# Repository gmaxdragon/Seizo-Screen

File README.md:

# Seizo Screen

Seizo Screen is a screen with a bunch of extra features that I find extremely useful for my robotic arm. There are lots of minor issues that are extremely annoying to work around, and this is my solution.

I want a screen so I can run direct motor controls without having to connect through my phone and worry about connections. I also wanted more features and wanted to make the whole thing look cooler.

## How I want to use it

During an arm session, I want to look at the screen and press a few buttons instead of doing everything on my phone. I want a "Run Arm" button that starts the arm setup. Keeping those controls on the arm would make it more independent. When this becomes a real product, I don't want using a phone to be required.

I want manual buttons for things like:

- Moving the base.
- Moving the wrist left and right.
- Opening and closing the gripper.
- Running the arm setup.

Eventually, I also want to let AI figure out the movements. The plan is to give it a prompt, have it convert that into individual movements, and then have the arm carry them out. This is something I'm planning to work on, and I think it would make everything much easier to use.

## The design challenge

One massive problem was organizing the components. I had to keep reorganizing them because none of the layouts seemed to be to my liking.

I originally had a much smaller PCB with fewer features. It felt like something that would take barely five minutes or so to put together, and it didn't seem cool enough to me. As a result, I changed it a lot by adding more features and making the PCB bigger.

I wanted things like a built-in meter and a breadboard area on the board. Making the PCB bigger gave me more room to do things like that. I'm planning to keep working on it and make it great.

## What I want to do next

Before the screen works with the arm, I need to do some basic sanity checks and make sure it works before connecting it to the arm. I might also try showing the Pi's output on it or adding some kind of built-in remote terminal, which would be extremely cool in my opinion.

I spent this summer designing and building the arm and worked on it almost every day. It has been extremely hard and difficult for me, and I want to make sure it works properly.

This has been my dream project for about a year, and I've struggled to find funding for all of it. I would really appreciate it if this project were accepted.

To be honest, soldering all the parts together by hand is extremely risky for me and it will take hours. I'd rather spend that time coding and making changes by hand and testing so I would like this to be presoldered please.

## Files

The Half-Life parts list had an 80-item (row) limit, so I used a grouped list for the submission. [Real_BOM.csv](Real_BOM.csv) contains the full ungrouped details, including each of the 150 fitted panel components, the screen, wiring and mounting items. It also identifies the matching HAT as a separate required dependency. [00-bom-halflife.csv](00-bom-halflife.csv) is the 27-row file for importing into Half-Life. Blank factory prices in the detailed BOM mean the quote is still pending, not that the parts are free.

- [Full detailed BOM](Real_BOM.csv)
- [KiCad project](szscreen.kicad_pro), [schematic](szscreen.kicad_sch) and [PCB](szscreen.kicad_pcb)
- [Schematic PDF](schematic.pdf)
- [Half-Life grouped BOM import](00-bom-halflife.csv) â€” 27 essential panel items within the 80-item limit; [import instructions](HALFLIFE-BOM-IMPORT.txt)
- [Earlier grouped project inventory](PROJECT-PARTS.csv) and [PCBWay preliminary price screenshot](quotes/pcbway/preliminary-calculator.png)
- [Parts list](BOM-panel.csv) and [connector pin map](CONNECTOR-PIN-MAP.csv)
- [Factory assembly BOM](assembly/BOM-PCBWay-panel.csv), [matching-HAT BOM](assembly/BOM-PCBWay-matching-HAT.csv), [DigiKey import CSV](assembly/DigiKey-panel-import.csv) and [assembly quote instructions](assembly/ORDER-INSTRUCTIONS.txt)
- [Factory quote upload ZIP](szscreen-PCBWay-turnkey-quote.zip)
- [Panel fabrication ZIP](szscreen-panel-Gerbers.zip)
- [Matching Pi HAT revision](matching-HAT/) and [assembly connections](ASSEMBLY-CONNECTIONS.txt)
- [Reference firmware](reference/firmware/) and [verification report](VERIFICATION.json)

## Contributions

The original schematic, PCB placement and full earlier routing were made by Vivaan, with his friend helping with ideas, parts, organization, routing and troubleshooting. ChatGPT/Codex helped with later schematic and PCB revisions, component and footprint selection, routing, checks and technical documentation. It generated the reference firmware from Vivaan's detailed behavior requirements. That code is reference only; Vivaan plans to write the actual implementation. The original earlier routing is preserved in [history/user-routed-rev19](history/user-routed-rev19/).

README narrative: my messages, with grammar and formatting fixed by AI.

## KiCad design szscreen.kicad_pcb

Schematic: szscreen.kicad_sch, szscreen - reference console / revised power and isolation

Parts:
C1, C2, C3, C4, C5, C6, C7, C8, C9, C10, C14, C16, C18, C19, C20, C21, C24, C25, C26, C28, C29, C31, C33, C34, C35, C36: 100n; C_Rect_L4.0mm_W2.5mm_P2.50mm
C15, C17, C30: 10u / 50V; CP_Radial_D5.0mm_P2.00mm
C22, C23: 1n; C_Rect_L4.0mm_W2.5mm_P2.50mm
C27: 4.7u / 50V; CP_Radial_D5.0mm_P2.00mm
C32: 100u / 16V; CP_Radial_D5.0mm_P2.00mm
D1: 3V3 POWER; LED_D3.0mm
D2: PROTO FAULT; LED_D3.0mm
D3, D4: BAT85; D_DO-35_SOD27_P7.62mm_Horizontal
D5: PROTO POWER; LED_D3.0mm
F1: MF-RHT050-0 / 500mA HOLD; Fuse_Bourns_MF-RHT050
H1, H2, H3, H4: M3 PANEL; MountingHole_3.2mm_M3
H5, H6, H7, H8: M3 LCD; MountingHole_3.2mm_M3
H9, H10, H11, H12: M2.5 PI STACK; MountingHole_2.7mm_M2.5
J1: TO HAT J7 / I2C AND IRQ; PinHeader_1x06_P2.54mm_Vertical
J2: WAVESHARE 16446 / 2.8in TOUCH; PinHeader_1x11_P2.54mm_Vertical
J3: AUX 1 / DRY NC ONLY; PinHeader_1x02_P2.54mm_Vertical
J4: AUX 2 / DRY NC ONLY; PinHeader_1x02_P2.54mm_Vertical
J5: TO HAT J6 / SPI; PinHeader_1x06_P2.54mm_Vertical
J6: TO HAT J5 / CONTROL; PinHeader_1x06_P2.54mm_Vertical
J7: 5V IN / FROM HAT J12; PinHeader_1x03_P2.54mm_Vertical
J8: EXISTING 5V FAN / PASS; PinHeader_1x03_P2.54mm_Vertical
J9: PROBE + / COMMON GND; PinHeader_1x02_P2.54mm_Vertical
J10: PROTO 5V / GND; PinHeader_1x02_P2.54mm_Vertical
J11: LCD ACTUAL VIO / GND TAP; PinHeader_1x02_P2.54mm_Vertical
J12: HAT J4.3 GPIO6 / J4.4 GPIO7; PinHeader_1x02_P2.54mm_Vertical
J13: HAT J10 POWER / 1 GND 2 3V3; PinHeader_1x02_P2.54mm_Vertical
K1: AQY212EH / INPUT DISCONNECT; DIP-4_W7.62mm
R1, R2, R3, R4, R5, R6, R7, R8, R17, R18, R31, R40, R41, R46, R47, R48, R58, R60, R68, R70, R71, R74, R75: 10k; R_Axial_DIN0207_L6.3mm_D2.5mm_P7.62mm_Horizontal
R9, R10, R11, R12, R13, R14, R15, R16, R19, R20, R49, R50, R51, R55, R61, R72: 1k; R_Axial_DIN0207_L6.3mm_D2.5mm_P7.62mm_Horizontal
R27, R28, R62: 2.2k; R_Axial_DIN0207_L6.3mm_D2.5mm_P7.62mm_Horizontal
R32, R33, R34, R63: 33; R_Axial_DIN0207_L6.3mm_D2.5mm_P7.62mm_Horizontal
R35, R36, R37, R38, R39, R56, R57, R64, R65, R66: 100; R_Axial_DIN0207_L6.3mm_D2.5mm_P7.62mm_Horizontal
R42, R69, R76, R77, R78, R79, R80, R81: 100k; R_Axial_DIN0207_L6.3mm_D2.5mm_P7.62mm_Horizontal
R43: 22k; R_Axial_DIN0207_L6.3mm_D2.5mm_P7.62mm_Horizontal
R44, R45, R73: 4.7k; R_Axial_DIN0207_L6.3mm_D2.5mm_P7.62mm_Horizontal
R52, R53: 49.9k / 0.1%; R_Axial_DIN0207_L6.3mm_D2.5mm_P10.16mm_Horizontal
R54: 10.0k / 0.1%; R_Axial_DIN0207_L6.3mm_D2.5mm_P10.16mm_Horizontal
R59: 330 / 1%; R_Axial_DIN0207_L6.3mm_D2.5mm_P7.62mm_Horizontal
R67: 210k / 1%; R_Axial_DIN0207_L6.3mm_D2.5mm_P10.16mm_Horizontal
SW1: F1; SW_TH_Tactile_Omron_B3F-100x
SW2: F2; SW_TH_Tactile_Omron_B3F-100x
SW3: F3; SW_TH_Tactile_Omron_B3F-100x
SW4: F4; SW_TH_Tactile_Omron_B3F-100x
SW5: F5; SW_TH_Tactile_Omron_B3F-100x
SW6: F6; SW_TH_Tactile_Omron_B3F-100x
SW7: F7; SW_TH_Tactile_Omron_B3F-100x
SW8: HOLD REQUEST; SW_TH_Tactile_Omron_B3F-100x
SW9: I/O RESET ONLY; SW_TH_Tactile_Omron_B3F-100x
SW10: F8; SW_TH_Tactile_Omron_B3F-100x
SW11: F9; SW_TH_Tactile_Omron_B3F-100x
SW12: F10; SW_TH_Tactile_Omron_B3F-100x
SW13: METER ENABLE; SW_CK_JS202011CQN_DPDT_Straight
SW14: PROTO 5V OFF / ON (100mA); SW_CK_JS202011CQN_DPDT_Straight
TP1: PANEL_3V3; TestPoint_THTPad_D1.5mm_Drill0.7mm
TP2: GND; TestPoint_THTPad_D1.5mm_Drill0.7mm
TP3: SCL; TestPoint_THTPad_D1.5mm_Drill0.7mm
TP4: SDA; TestPoint_THTPad_D1.5mm_Drill0.7mm
TP5: IO_RESET; TestPoint_THTPad_D1.5mm_Drill0.7mm
TP6: LCD_5V; TestPoint_THTPad_D1.5mm_Drill0.7mm
U1: MCP23017-E/SP / 0x20; DIP-28_W7.62mm
U2: MCP3202-BI/P; DIP-8_W7.62mm
U3: MCP6002-I/P; DIP-8_W7.62mm
U4: MCP1525-I/TO; TO-92_Inline_Wide
U5: TPS2553DBVR-1 / LATCH OFF; SOT-23-6
U6: Adafruit 4683 3V3 BUCK; PinHeader_1x04_P2.54mm_Vertical
U8, U9, U10: SN74LV125AN; DIP-14_W7.62mm
U11: SN74AHC14N; DIP-14_W7.62mm

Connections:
/ADC_CH0: C22.1, R56.2, U2.2 (CH0)
/ADC_CH1: C23.1, R57.2, U2.3 (CH1)
/ADC_CS: R58.2, R66.2, U2.1 (~CS/SHDN)
/ADC_MISO: R63.1, U2.6 (DOUT)
/ADC_MOSI: R64.2, U2.5 (DIN)
/ADC_SCLK: R65.2, U2.7 (CLK)
/BB_EN: R69.1, SW14.2 (B), U5.3 (EN)
/BB_FAULT: D2.1 (K), J12.2, R70.2, U5.4 (~FAULT)
/BB_ILIM: R67.1, U5.5 (ILIM)
/BB_ON: R68.2, SW14.1 (A)
/BTN1: R9.2, U1.21 (GPA0)
/BTN2: R10.2, U1.22 (GPA1)
/BTN3: R11.2, U1.23 (GPA2)
/BTN4: R12.2, U1.24 (GPA3)
/BTN5: R13.2, U1.25 (GPA4)
/BTN6: R14.2, U1.26 (GPA5)
/BTN7: R15.2, U1.27 (GPA6)
/BTN8: R49.2, U1.4 (GPB3)
/BTN9: R50.2, U1.5 (GPB4)
/BTN10: R51.2, U1.6 (GPB5)
/GND: C1.2, C2.2, C3.2, C4.2, C5.2, C6.2, C7.2, C8.2, C9.2, C10.2, C14.2, C15.2, C16.2, C17.2, C18.2, C19.2, C20.2, C21.2, C22.2, C23.2, C24.2, C25.2, C26.2, C27.2, C28.2, C29.2, C30.2, C31.2, C32.2, C33.2, C34.2, C35.2, C36.2, D1.1 (K), D3.2 (A), D5.1 (K), J1.6, J2.2, J3.2, J4.2, J5.6, J6.6, J7.2, J8.2, J9.2, J10.2, J11.2, J13.1, K1.2, R42.1, R54.2, R67.2, R69.2, R71.2, R73.2, R76.2, R77.2, R78.2, R79.2, R80.2, R81.2, SW1.2, SW2.2, SW3.2, SW4.2, SW5.2, SW6.2, SW7.2, SW8.2, SW9.2, SW10.2, SW11.2, SW12.2, SW13.4 (A), SW14.3 (C), TP2.1, U1.10 (V_{SS}), U1.15 (A0), U1.16 (A1), U1.17 (A2), U2.4 (VSS), U3.4 (V-), U4.1 (Vss), U5.2 (GND), U6.1, U8.7 (GND), U9.7 (GND), U9.12, U10.4, U10.5, U10.7 (GND), U10.9, U10.12, U11.7 (GND), U11.11, U11.13
/HAT_ADC_CS: J1.4, R66.1
/HAT_LCD_BL: J6.3, R80.1, U9.5
/HAT_LCD_CS: J5.4, R74.2, U8.9
/HAT_LCD_DC: J6.1, R78.1, U8.12
/HAT_LCD_RST: J6.2, R79.1, U9.2
/HAT_MISO: J5.1, R32.1, R63.2
/HAT_MOSI: J5.2, R64.1, R76.1, U8.2
/HAT_SCLK: J5.3, R65.1, R77.1, U8.5
/HAT_TP_CS: J6.4, R75.2, U9.9, U10.1
/HAT_TP_IRQ: J1.3, U11.4
/HOLD_IN: R16.2, U1.1 (GPB0)
/HOLD_RAW: C8.1, R8.2, R16.1, SW8.1
/IO_RESET: R31.2, SW9.1, TP5.1, U1.18 (~RESET)
/IRQ_INVERTED: U11.2, U11.3
/ISO_LCD_BL: R38.1, U9.6
/ISO_LCD_CS: R35.1, U8.8
/ISO_LCD_DC: R36.1, U8.11
/ISO_LCD_RST: R37.1, U9.3
/ISO_MISO: R32.2, U10.3
/ISO_MOSI: R33.1, U8.3
/ISO_SCLK: R34.1, U8.6
/ISO_TP_CS: R39.1, U9.8
/KEY1: C1.1, R1.2, R9.1, SW1.1
/KEY2: C2.1, R2.2, R10.1, SW2.1
/KEY3: C3.1, R3.2, R11.1, SW3.1
/KEY4: C4.1, R4.2, R12.1, SW4.1
/KEY5: C5.1, R5.2, R13.1, SW5.1
/KEY6: C6.1, R6.2, R14.1, SW6.1
/KEY7: C7.1, R7.2, R15.1, SW7.1
/KEY8: C18.1, R46.2, R49.1, SW10.1
/KEY9: C19.1, R47.2, R50.1, SW11.1
/KEY10: C20.1, R48.2, R51.1, SW12.1
/LCD_5V: C16.1, C17.1, F1.2, J2.1, TP6.1
/LCD_BL: J2.9, R38.2, R42.2
/LCD_CS: J2.6, R35.2, R40.2
/LCD_DC: J2.7, R36.2
/LCD_MISO_RAW: J2.3, R81.1, U10.2
/LCD_MOSI: J2.4, R33.2
/LCD_OE_N: R72.2, U8.1, U8.4, U8.10, U8.13, U9.1, U9.4, U9.10, U10.6
/LCD_RST: J2.8, R37.2
/LCD_SCLK: J2.5, R34.2
/LCD_TP_IRQ_RAW: J2.11, R43.2, U11.1
/LCD_VIO: C33.1, C34.1, J11.1, R40.1, R41.1, R43.1, R72.1, R73.1, U8.14 (VCC), U9.13, U9.14 (VCC), U11.5
/LCD_VIO_ABSENT: U11.6, U11.9
/LCD_VIO_PRESENT: J12.1, U11.8
/LED1_A: D1.2 (A), R27.2
/LED2_A: D2.2 (A), R28.2
/METER_AMP_IN: D3.1 (K), D4.2 (A), R55.2, U3.3 (+)
/METER_BUFFER: R56.1, U3.1, U3.2 (-)
/METER_DIV: C21.1, R53.2, R54.1, R55.1
/METER_EN_IN: R61.2, U1.7 (GPB6)
/METER_EN_RAW: C28.1, R60.2, R61.1, SW13.5 (B)
/METER_LED_SUPPLY: R59.1, SW13.2 (B)
/METER_PROBE_PLUS: J9.1, K1.3
/METER_RELAY_A: K1.1, R59.2
/METER_RMID: R52.2, R53.1
/METER_SWITCHED: K1.4, R52.1
/PANEL_3V3: C14.1, C15.1, C24.1, C25.1, C26.1, C35.1, C36.1, D4.1 (K), J1.5, J5.5, J6.5, J13.2, R1.1, R2.1, R3.1, R4.1, R5.1, R6.1, R7.1, R8.1, R17.1, R18.1, R27.1, R28.1, R31.1, R44.1, R45.1, R46.1, R47.1, R48.1, R58.1, R60.1, R70.1, R74.1, R75.1, SW13.1 (A), TP1.1, U1.9 (V_{DD}), U2.8 (VDD/VREF), U3.8 (V+), U4.3 (Vin), U6.2, U10.10, U10.13, U10.14 (VCC), U11.14 (VCC)
/PI_5V_IN: C31.1, C32.1, F1.1, J7.1, J8.1, R68.1, U5.1 (IN), U6.3
/PROTO_5V: C29.1, C30.1, J10.1, R62.1, R71.1, U5.6 (OUT)
/PROTO_LED_A: D5.2 (A), R62.2
/REF_2V5: C27.1, U3.5 (+), U4.2 (Vout)
/REF_BUFFER: R57.1, U3.6 (-), U3.7
/SCL: J1.1, R44.2, TP3.1, U1.12 (SCK)
/SDA: J1.2, R45.2, TP4.1, U1.13 (SDA)
/STOP1_IN: C9.1, R19.2, U1.2 (GPB1)
/STOP1_RAW: J3.1, R17.2, R19.1
/STOP2_IN: C10.1, R20.2, U1.3 (GPB2)
/STOP2_RAW: J4.1, R18.2, R20.1
/TP_CS: J2.10, R39.2, R41.2

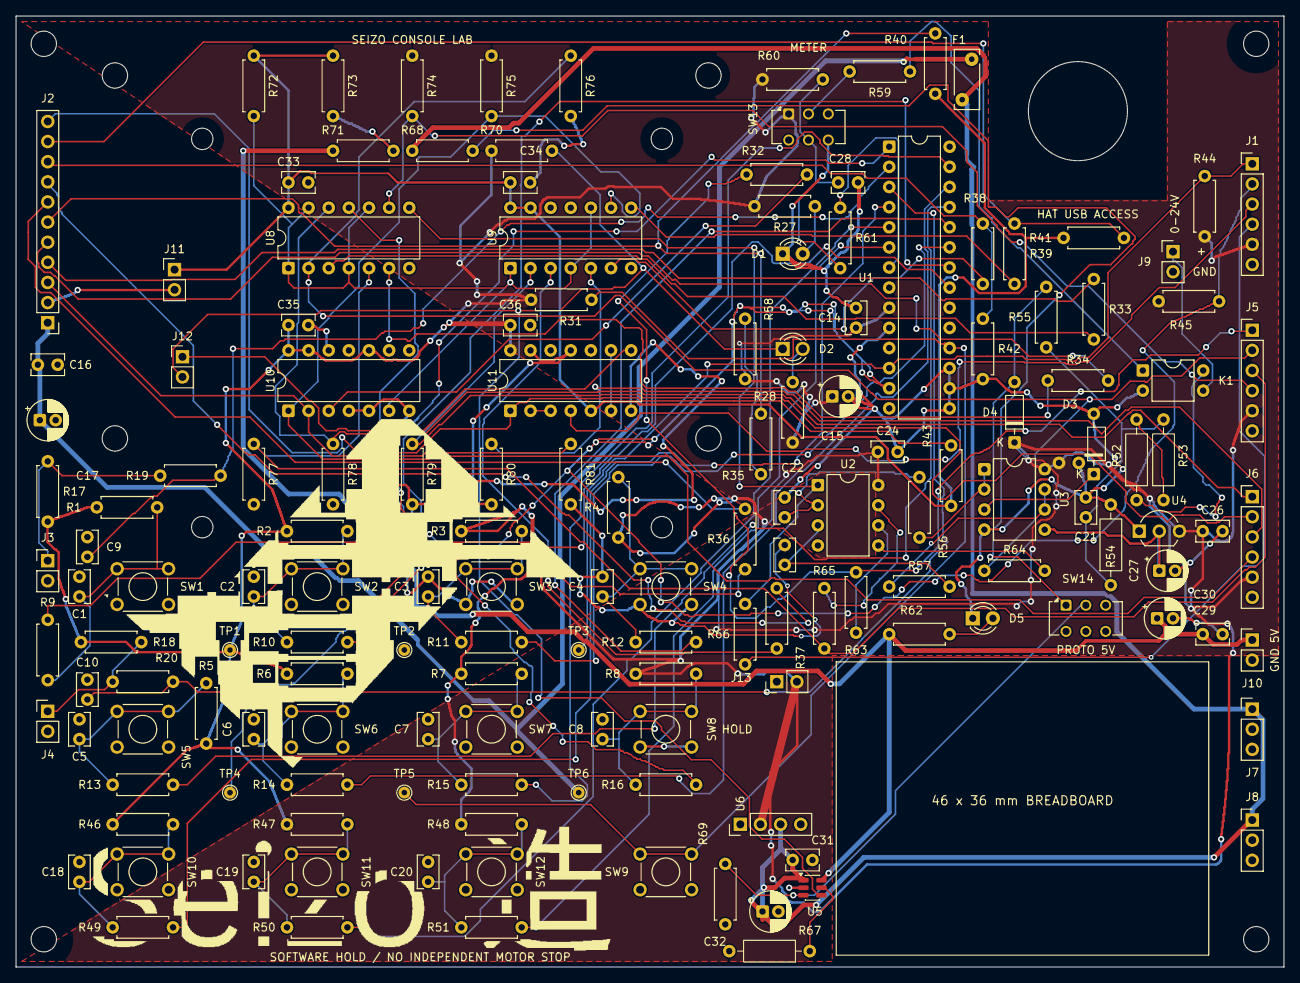
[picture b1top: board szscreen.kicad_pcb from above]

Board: 2 copper layers, 160.0 x 120.0 mm, 168 parts (1 on the bottom side), 91 nets.

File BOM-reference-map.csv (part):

Reference,Value,Schematic_footprint,Selected_part,Purchase_group
C1,100n,Capacitor_THT:C_Rect_L4.0mm_W2.5mm_P2.50mm,C315C104K5R5TA,C1 C2 C3 C4 C5 C6 C7 C8 C9 C10 C14 C16 C18 C19 C20 C21 C24 C25 C26 C28 C29 C31 C33 C34 C35 C36
C10,100n,Capacitor_THT:C_Rect_L4.0mm_W2.5mm_P2.50mm,C315C104K5R5TA,C1 C2 C3 C4 C5 C6 C7 C8 C9 C10 C14 C16 C18 C19 C20 C21 C24 C25 C26 C28 C29 C31 C33 C34 C35 C36
C14,100n,Capacitor_THT:C_Rect_L4.0mm_W2.5mm_P2.50mm,C315C104K5R5TA,C1 C2 C3 C4 C5 C6 C7 C8 C9 C10 C14 C16 C18 C19 C20 C21 C24 C25 C26 C28 C29 C31 C33 C34 C35 C36
C15,10u / 50V,Capacitor_THT:CP_Radial_D5.0mm_P2.00mm,EEU-FR1H100,C15 C17 C30
C16,100n,Capacitor_THT:C_Rect_L4.0mm_W2.5mm_P2.50mm,C315C104K5R5TA,C1 C2 C3 C4 C5 C6 C7 C8 C9 C10 C14 C16 C18 C19 C20 C21 C24 C25 C26 C28 C29 C31 C33 C34 C35 C36
C17,10u / 50V,Capacitor_THT:CP_Radial_D5.0mm_P2.00mm,EEU-FR1H100,C15 C17 C30
C18,100n,Capacitor_THT:C_Rect_L4.0mm_W2.5mm_P2.50mm,C315C104K5R5TA,C1 C2 C3 C4 C5 C6 C7 C8 C9 C10 C14 C16 C18 C19 C20 C21 C24 C25 C26 C28 C29 C31 C33 C34 C35 C36
C19,100n,Capacitor_THT:C_Rect_L4.0mm_W2.5mm_P2.50mm,C315C104K5R5TA,C1 C2 C3 C4 C5 C6 C7 C8 C9 C10 C14 C16 C18 C19 C20 C21 C24 C25 C26 C28 C29 C31 C33 C34 C35 C36
C2,100n,Capacitor_THT:C_Rect_L4.0mm_W2.5mm_P2.50mm,C315C104K5R5TA,C1 C2 C3 C4 C5 C6 C7 C8 C9 C10 C14 C16 C18 C19 C20 C21 C24 C25 C26 C28 C29 C31 C33 C34 C35 C36
C20,100n,Capacitor_THT:C_Rect_L4.0mm_W2.5mm_P2.50mm,C315C104K5R5TA,C1 C2 C3 C4 C5 C6 C7 C8 C9 C10 C14 C16 C18 C19 C20 C21 C24 C25 C26 C28 C29 C31 C33 C34 C35 C36
C21,100n,Capacitor_THT:C_Rect_L4.0mm_W2.5mm_P2.50mm,C315C104K5R5TA,C1 C2 C3 C4 C5 C6 C7 C8 C9 C10 C14 C16 C18 C19 C20 C21 C24 C25 C26 C28 C29 C31 C33 C34 C35 C36
C22,1n,Capacitor_THT:C_Rect_L4.0mm_W2.5mm_P2.50mm,C315C102J1G5TA,C22 C23
C23,1n,Capacitor_THT:C_Rect_L4.0mm_W2.5mm_P2.50mm,C315C102J1G5TA,C22 C23
C24,100n,Capacitor_THT:C_Rect_L4.0mm_W2.5mm_P2.50mm,C315C104K5R5TA,C1 C2 C3 C4 C5 C6 C7 C8 C9 C10 C14 C16 C18 C19 C20 C21 C24 C25 C26 C28 C29 C31 C33 C34 C35 C36
C25,100n,Capacitor_THT:C_Rect_L4.0mm_W2.5mm_P2.50mm,C315C104K5R5TA,C1 C2 C3 C4 C5 C6 C7 C8 C9 C10 C14 C16 C18 C19 C20 C21 C24 C25 C26 C28 C29 C31 C33 C34 C35 C36
C26,100n,Capacitor_THT:C_Rect_L4.0mm_W2.5mm_P2.50mm,C315C104K5R5TA,C1 C2 C3 C4 C5 C6 C7 C8 C9 C10 C14 C16 C18 C19 C20 C21 C24 C25 C26 C28 C29 C31 C33 C34 C35 C36
C27,4.7u / 50V,Capacitor_THT:CP_Radial_D5.0mm_P2.00mm,50YXJ4.7M5X11,C27
C28,100n,Capacitor_THT:C_Rect_L4.0mm_W2.5mm_P2.50mm,C315C104K5R5TA,C1 C2 C3 C4 C5 C6 C7 C8 C9 C10 C14 C16 C18 C19 C20 C21 C24 C25 C26 C28 C29 C31 C33 C34 C35 C36
C29,100n,Capacitor_THT:C_Rect_L4.0mm_W2.5mm_P2.50mm,C315C104K5R5TA,C1 C2 C3 C4 C5 C6 C7 C8 C9 C10 C14 C16 C18 C19 C20 C21 C24 C25 C26 C28 C29 C31 C33 C34 C35 C36
C3,100n,Capacitor_THT:C_Rect_L4.0mm_W2.5mm_P2.50mm,C315C104K5R5TA,C1 C2 C3 C4 C5 C6 C7 C8 C9 C10 C14 C16 C18 C19 C20 C21 C24 C25 C26 C28 C29 C31 C33 C34 C35 C36
C30,10u / 50V,Capacitor_THT:CP_Radial_D5.0mm_P2.00mm,EEU-FR1H100,C15 C17 C30
C31,100n,Capacitor_THT:C_Rect_L4.0mm_W2.5mm_P2.50mm,C315C104K5R5TA,C1 C2 C3 C4 C5 C6 C7 C8 C9 C10 C14 C16 C18 C19 C20 C21 C24 C25 C26 C28 C29 C31 C33 C34 C35 C36
C32,100u / 16V,Capacitor_THT:CP_Radial_D5.0mm_P2.00mm,EEU-FR1C101,C32
C33,100n,Capacitor_THT:C_Rect_L4.0mm_W2.5mm_P2.50mm,C315C104K5R5TA,C1 C2 C3 C4 C5 C6 C7 C8 C9 C10 C14 C16 C18 C19 C20 C21 C24 C25 C26 C28 C29 C31 C33 C34 C35 C36
C34,100n,Capacitor_THT:C_Rect_L4.0mm_W2.5mm_P2.50mm,C315C104K5R5TA,C1 C2 C3 C4 C5 C6 C7 C8 C9 C10 C14 C16 C18 C19 C20 C21 C24 C25 C26 C28 C29 C31 C33 C34 C35 C36
C35,100n,Capacitor_THT:C_Rect_L4.0mm_W2.5mm_P2.50mm,C315C104K5R5TA,C1 C2 C3 C4 C5 C6 C7 C8 C9 C10 C14 C16 C18 C19 C20 C21 C24 C25 C26 C28 C29 C31 C33 C34 C35 C36
C36,100n,Capacitor_THT:C_Rect_L4.0mm_W2.5mm_P2.50mm,C315C104K5R5TA,C1 C2 C3 C4 C5 C6 C7 C8 C9 C10 C14 C16 C18 C19 C20 C21 C24 C25 C26 C28 C29 C31 C33 C34 C35 C36
C4,100n,Capacitor_THT:C_Rect_L4.0mm_W2.5mm_P2.50mm,C315C104K5R5TA,C1 C2 C3 C4 C5 C6 C7 C8 C9 C10 C14 C16 C18 C19 C20 C21 C24 C25 C26 C28 C29 C31 C33 C34 C35 C36
C5,100n,Capacitor_THT:C_Rect_L4.0mm_W2.5mm_P2.50mm,C315C104K5R5TA,C1 C2 C3 C4 C5 C6 C7 C8 C9 C10 C14 C16 C18 C19 C20 C21 C24 C25 C26 C28 C29 C31 C33 C34 C35 C36
C6,100n,Capacitor_THT:C_Rect_L4.0mm_W2.5mm_P2.50mm,C315C104K5R5TA,C1 C2 C3 C4 C5 C6 C7 C8 C9 C10 C14 C16 C18 C19 C20 C21 C24 C25 C26 C28 C29 C31 C33 C34 C35 C36
C7,100n,Capacitor_THT:C_Rect_L4.0mm_W2.5mm_P2.50mm,C315C104K5R5TA,C1 C2 C3 C4 C5 C6 C7 C8 C9 C10 C14 C16 C18 C19 C20 C21 C24 C25 C26 C28 C29 C31 C33 C34 C35 C36
C8,100n,Capacitor_THT:C_Rect_L4.0mm_W2.5mm_P2.50mm,C315C104K5R5TA,C1 C2 C3 C4 C5 C6 C7 C8 C9 C10 C14 C16 C18 C19 C20 C21 C24 C25 C26 C28 C29 C31 C33 C34 C35 C36
C9,100n,Capacitor_THT:C_Rect_L4.0mm_W2.5mm_P2.50mm,C315C104K5R5TA,C1 C2 C3 C4 C5 C6 C7 C8 C9 C10 C14 C16 C18 C19 C20 C21 C24 C25 C26 C28 C29 C31 C33 C34 C35 C36
D1,3V3 POWER,LED_THT:LED_D3.0mm,WP3A8GD,D1 D5
D2,PROTO FAULT,LED_THT:LED_D3.0mm,WP3A8ID,D2
D3,BAT85,Diode_THT:D_DO-35_SOD27_P7.62mm_Horizontal,BAT85S-TAP,D3 D4
D4,BAT85,Diode_THT:D_DO-35_SOD27_P7.62mm_Horizontal,BAT85S-TAP,D3 D4
D5,PROTO POWER,LED_THT:LED_D3.0mm,WP3A8GD,D1 D5
F1,MF-RHT050-0 / 500mA HOLD,Fuse:Fuse_Bourns_MF-RHT050,MF-RHT050-0,F1
H1,M3 PANEL,MountingHole:MountingHole_3.2mm_M3,BARE MOUNTING HOLE - NO ELECTRONIC PART,H1 H2 H3 H4 H5 H6 H7 H8 H9 H10 H11 H12
H10,M2.5 PI STACK,MountingHole:MountingHole_2.7mm_M2.5,BARE MOUNTING HOLE - NO ELECTRONIC PART,H1 H2 H3 H4 H5 H6 H7 H8 H9 H10 H11 H12
H11,M2.5 PI STACK,MountingHole:MountingHole_2.7mm_M2.5,BARE MOUNTING HOLE - NO ELECTRONIC PART,H1 H2 H3 H4 H5 H6 H7 H8 H9 H10 H11 H12
H12,M2.5 PI STACK,MountingHole:MountingHole_2.7mm_M2.5,BARE MOUNTING HOLE - NO ELECTRONIC PART,H1 H2 H3 H4 H5 H6 H7 H8 H9 H10 H11 H12
H2,M3 PANEL,MountingHole:MountingHole_3.2mm_M3,BARE MOUNTING HOLE - NO ELECTRONIC PART,H1 H2 H3 H4 H5 H6 H7 H8 H9 H10 H11 H12
H3,M3 PANEL,MountingHole:MountingHole_3.2mm_M3,BARE MOUNTING HOLE - NO ELECTRONIC PART,H1 H2 H3 H4 H5 H6 H7 H8 H9 H10 H11 H12
H4,M3 PANEL,MountingHole:MountingHole_3.2mm_M3,BARE MOUNTING HOLE - NO ELECTRONIC PART,H1 H2 H3 H4 H5 H6 H7 H8 H9 H10 H11 H12
H5,M3 LCD,MountingHole:MountingHole_3.2mm_M3,BARE MOUNTING HOLE - NO ELECTRONIC PART,H1 H2 H3 H4 H5 H6 H7 H8 H9 H10 H11 H12
H6,M3 LCD,MountingHole:MountingHole_3.2mm_M3,BARE MOUNTING HOLE - NO ELECTRONIC PART,H1 H2 H3 H4 H5 H6 H7 H8 H9 H10 H11 H12
H7,M3 LCD,MountingHole:MountingHole_3.2mm_M3,BARE MOUNTING HOLE - NO ELECTRONIC PART,H1 H2 H3 H4 H5 H6 H7 H8 H9 H10 H11 H12
H8,M3 LCD,MountingHole:MountingHole_3.2mm_M3,BARE MOUNTING HOLE - NO ELECTRONIC PART,H1 H2 H3 H4 H5 H6 H7 H8 H9 H10 H11 H12
H9,M2.5 PI STACK,MountingHole:MountingHole_2.7mm_M2.5,BARE MOUNTING HOLE - NO ELECTRONIC PART,H1 H2 H3 H4 H5 H6 H7 H8 H9 H10 H11 H12
J1,TO HAT J7 / I2C AND IRQ,Connector_PinHeader_2.54mm:PinHeader_1x06_P2.54mm_Vertical,PRPC040SAAN-RC,J1 J2 J3 J4 J5 J6 J7 J8 J9 J10 J11 J12 J13
J10,PROTO 5V / GND,Connector_PinHeader_2.54mm:PinHeader_1x02_P2.54mm_Vertical,PRPC040SAAN-RC,J1 J2 J3 J4 J5 J6 J7 J8 J9 J10 J11 J12 J13
J11,LCD ACTUAL VIO / GND TAP,Connector_PinHeader_2.54mm:PinHeader_1x02_P2.54mm_Vertical,PRPC040SAAN-RC,J1 J2 J3 J4 J5 J6 J7 J8 J9 J10 J11 J12 J13
J12,HAT J4.3 GPIO6 / J4.4 GPIO7,Connector_PinHeader_2.54mm:PinHeader_1x02_P2.54mm_Vertical,PRPC040SAAN-RC,J1 J2 J3 J4 J5 J6 J7 J8 J9 J10 J11 J12 J13
J13,HAT J10 POWER / 1 GND 2 3V3,Connector_PinHeader_2.54mm:PinHeader_1x02_P2.54mm_Vertical,PRPC040SAAN-RC,J1 J2 J3 J4 J5 J6 J7 J8 J9 J10 J11 J12 J13
J2,WAVESHARE 16446 / 2.8in TOUCH,Connector_PinHeader_2.54mm:PinHeader_1x11_P2.54mm_Vertical,PRPC040SAAN-RC,J1 J2 J3 J4 J5 J6 J7 J8 J9 J10 J11 J12 J13
J3,AUX 1 / DRY NC ONLY,Connector_PinHeader_2.54mm:PinHeader_1x02_P2.54mm_Vertical,PRPC040SAAN-RC,J1 J2 J3 J4 J5 J6 J7 J8 J9 J10 J11 J12 J13
J4,AUX 2 / DRY NC ONLY,Connector_PinHeader_2.54mm:PinHeader_1x02_P2.54mm_Vertical,PRPC040SAAN-RC,J1 J2 J3 J4 J5 J6 J7 J8 J9 J10 J11 J12 J13
J5,TO HAT J6 / SPI,Connector_PinHeader_2.54mm:PinHeader_1x06_P2.54mm_Vertical,PRPC040SAAN-RC,J1 J2 J3 J4 J5 J6 J7 J8 J9 J10 J11 J12 J13
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
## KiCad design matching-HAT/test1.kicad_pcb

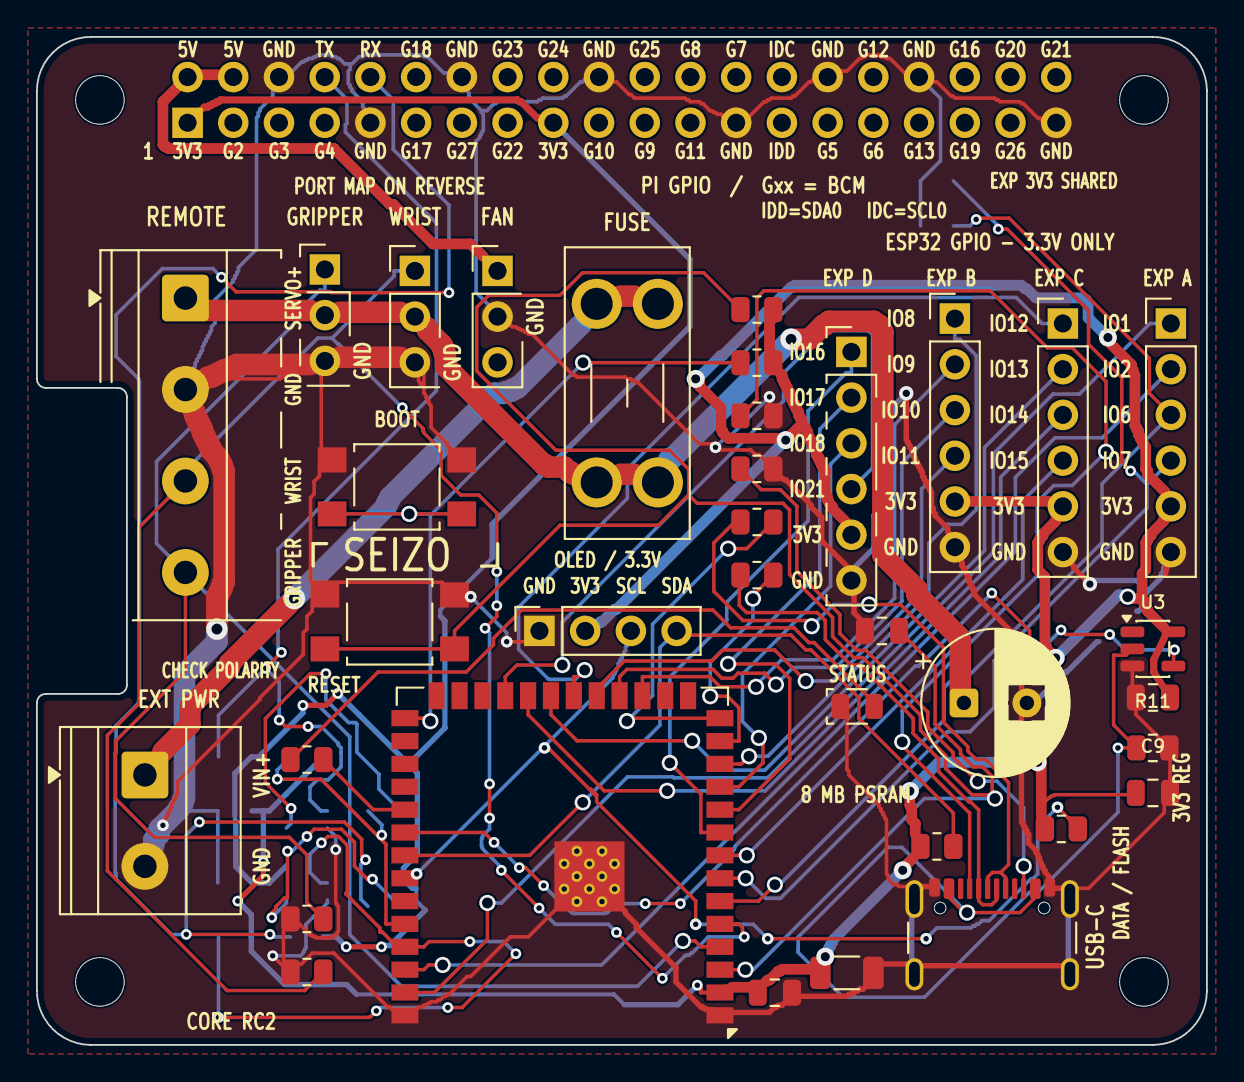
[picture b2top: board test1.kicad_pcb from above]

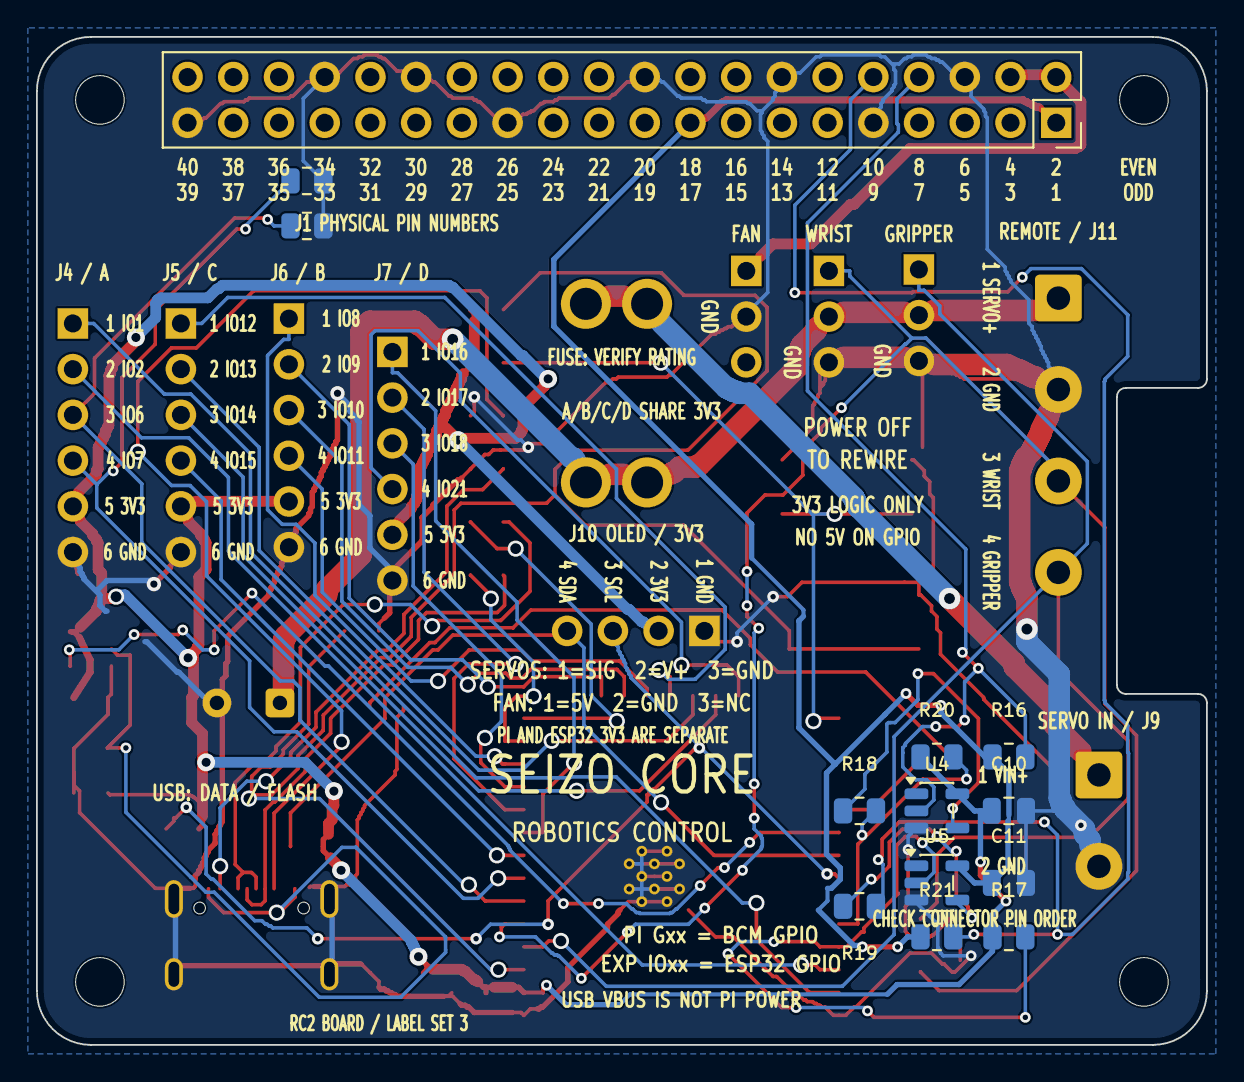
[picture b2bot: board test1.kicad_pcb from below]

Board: 2 copper layers, 65.0 x 56.0 mm, 52 parts (13 on the bottom side), 44 nets.

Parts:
C2: 1uF; RC2_C2_C_0805_2012Metric
C3: 470uF; RC2_C3_CP_Radial_D8_0mm_P3_50mm
C4: 22uF; RC2_C4_C_1206_3216Metric
C5: 100nF; RC2_C5_C_0805_2012Metric
C8: 1uF; RC2_C8_C_0805_2012Metric
C9, C10, C11: 100nF; C_0805_2012Metric
D1: LED; RC2_D1_LED_0805_2012Metric
F1: Fuse; RC2_F1_Fuseholder_Blade_Mini_Keystone_3568
J1: GPIO; Pi_HAT_Stacking_Socket_Checked
J2: Gripper; RC2_J2_PinHeader_1x03_P2_54mm_Vertical
J3: Wrist; RC2_J3_PinHeader_1x03_P2_54mm_Vertical
J4: Conn_01x06; RC2_J4_PinHeader_1x06_P2_54mm_Vertical
J5: Conn_01x06; RC2_J5_PinHeader_1x06_P2_54mm_Vertical
J6: Conn_01x06; RC2_J6_PinHeader_1x06_P2_54mm_Vertical
J7: Conn_01x06; RC2_J7_PinHeader_1x06_P2_54mm_Vertical
J8: USB_C_Receptacle_USB2.0_16P; RC2_J8_USB4105_GND_Heel_Clearance
J9: Screw_Terminal_01x02; RC2_J9_TerminalBlock_Phoenix_MKDS_1_5_2_5_08_1x02_P5_08mm_H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
J10: ONBOARD_OLED; RC2_J10_PinSocket_1x04_P2_54mm_Vertical
J11: REMOTE_SERVO_CABLE; RC2_J11_Servo_Terminal_Silk_Clipped
J12: PI_FAN; RC2_J12_PinHeader_1x03_P2_54mm_Vertical
MH1, MH2, MH3, MH4: MountingHole_2.7mm_M2.5
R3: 10K; RC2_R3_R_0805_2012Metric
R4: 10k; RC2_R4_R_0805_2012Metric
R5: 5.1k; RC2_R5_R_0805_2012Metric
R6: 5.1k; RC2_R6_R_0805_2012Metric
R7: 22; RC2_R7_R_0805_2012Metric
R8: 22; RC2_R8_R_0805_2012Metric
R9: 1k; RC2_R9_R_0805_2012Metric
R11, R16, R17, R20, R21, R22, R23: 100k; R_0805_2012Metric
R12: 10k; RC2_R12_R_0805_2012Metric
R13: 10k; RC2_R13_R_0805_2012Metric
R14: 4.7k; RC2_R14_R_0805_2012Metric
R15: 4.7k; RC2_R15_R_0805_2012Metric
R18, R19: 33; R_0805_2012Metric
RESET1: SW_Push; RC2_RESET1_SW_SPST_TL3305A
SW1: SW_Push; RC2_SW1_SW_SPST_TL3305A
U2: ESP32-S3-WROOM-1-N8R8; RC2_U2_ESP32_S3_WROOM_1_Thermal030
U3, U4, U5: SN74LVC1G17DBVR; SOT-23-5

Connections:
+3V3: C11.1, J1.1, J1.17, R16.1, R21.1, U5.5
+5V: J1.2, J1.4, J12.1
/BOARD_3V3: C4.1, C5.1, C8.1, C9.1, C10.1, J4.5, J5.5, J6.5, J7.5, J10.2, R3.2, R4.2, R14.1, R15.1, R17.1, R20.1, U2.2 (3V3), U3.5, U4.5
/ESP_UART_RX: R18.2, R20.2, U2.36 (RXD0)
/ESP_UART_TX: R17.2, U2.37 (TXD0), U5.2
/GPIO_A1: J4.1, U2.39 (IO1)
/GPIO_A2: J4.2, U2.38 (IO2)
/GPIO_A3: J4.3, R22.1, U2.6 (IO6)
/GPIO_A4: J4.4, R23.1, U2.7 (IO7)
/GPIO_B1: J6.1, U2.12 (IO8)
/GPIO_B2: J6.2, U2.17 (IO9)
/GPIO_B3: J6.3, U2.18 (IO10)
/GPIO_B4: J6.4, U2.19 (IO11)
/GPIO_C1: J5.1, U2.20 (IO12)
/GPIO_C2: J5.2, U2.21 (IO13)
/GPIO_C3: J5.3, U2.22 (IO14)
/GPIO_C4: J5.4, U2.8 (IO15)
/GPIO_D1: J7.1, U2.9 (IO16)
/GPIO_D2: J7.2, U2.10 (IO17)
/GPIO_D3: J7.3, U2.11 (IO18)
/GPIO_D4: J7.4, U2.23 (IO21)
/GRIPPER_SIG: J2.1, J11.4, R12.2, U2.4 (IO4)
/IO19: R8.2, U2.13 (USB_D-)
/IO20: R7.2, U2.14 (USB_D+)
/OLED_SCL: J10.3, R15.2, U2.34 (IO41)
/OLED_SDA: J10.4, R14.2, U2.33 (IO40)
/PI_UART_RX: J1.10, R19.2, R21.2
/PI_UART_TX: J1.8, R16.2, U4.2
/SERVO_IN+: F1.2, J9.1
/SERVO_V+: C3.1, F1.1, J2.2, J3.2, J11.1
/STATUS_LED: R9.2, U2.31 (IO38)
/UART_TO_ESP_BUF: R18.1, U4.4
/UART_TO_PI_BUF: R19.1, U5.4
/USB-VBUS_SENSE: U2.32 (IO39), U3.4
/USB_VBUS_RAW: J8.A4 (VBUS), J8.A9 (VBUS), J8.B4 (VBUS), J8.B9 (VBUS), R11.1, U3.2
/WRIST_SIG: J3.1, J11.3, R13.2, U2.5 (IO5)
GND: C2.1, C3.2, C4.2, C5.2, C8.2, C9.2, C10.2, C11.2, D1.1 (K), J1.6, J1.9, J1.14, J1.20, J1.25, J1.30, J1.34, J1.39, J2.3, J3.3, J4.6, J5.6, J6.6, J7.6, J8.A1 (GND), J8.A12 (GND), J8.B1 (GND), J8.B12 (GND), J8.SH (SHIELD), J9.2, J10.1, J11.2, J12.2, R5.2, R6.2, R11.2, R12.1, R13.1, R22.2, R23.2, RESET1.1, SW1.1, U2.1 (GND), U2.40 (GND), U2.41 (GND), U3.3, U4.3, U5.3
unnamed: D1.2 (A), R9.1
unnamed: J8.A5 (CC1), R5.1
unnamed: J8.B5 (CC2), R6.1
unnamed: J8.A6 (D+), J8.B6 (D+), R7.1
unnamed: J8.A7 (D-), J8.B7 (D-), R8.1
unnamed: C2.2, R3.1, RESET1.2, U2.3 (EN)
unnamed: R4.1, SW1.2, U2.27 (IO0)

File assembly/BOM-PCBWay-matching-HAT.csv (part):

Item,Quantity Per PCB,Reference Designator,Manufacturer,Manufacturer Part Number,Distributor Part Number,Description,Package,Type,Side,Supplier URL,Assembly Notes
1,1,J11,Phoenix Contact,1715747,277-1265-ND,4-position 5.08 mm terminal,Seizo_Reviewed:RC2_J11_Servo_Terminal_Silk_Clipped,THT,Top,,"ONE terminal on this HAT; no separate extension board in this quotation. Carried-forward exact selection; assembler must confirm land pattern, availability and orientation. No unapproved substitutions."
2,1,J9,Phoenix Contact,1715721,277-1263-ND,2-position 5.08 mm terminal,Seizo_Reviewed:RC2_J9_TerminalBlock_Phoenix_MKDS_1_5_2_5_08_1x02_P5_08mm_Horizontal,THT,Top,,"Servo supply inlet Carried-forward exact selection; assembler must confirm land pattern, availability and orientation. No unapproved substitutions."
3,1,J10,Samtec,SSW-104-01-G-S,612-SSW-104-01-G-S-ND,4-position 2.54mm female power/I2C socket,Seizo_Reviewed:RC2_J10_PinSocket_1x04_P2_54mm_Vertical,THT,Top,,"Pin1 GND, pin2 BOARD_3V3, pins3/4 reserved I2C. Panel power pair uses pins1/2. No extra OLED purchased. Carried-forward exact selection; assembler must confirm land pattern, availability and orientation. No unapproved substitutions."
4,1,C3,Panasonic,EEU-FR1A471,P124219-ND,470uF 10V radial 3.50mm pitch,Seizo_Reviewed:RC2_C3_CP_Radial_D8_0mm_P3_50mm,THT,Top,,"Polarized Carried-forward exact selection; assembler must confirm land pattern, availability and orientation. No unapproved substitutions."
5,1,F1,Keystone Electronics,3568,36-3568-ND,PCB MINI blade fuse holder,Seizo_Reviewed:RC2_F1_Fuseholder_Blade_Mini_Keystone_3568,THT,Top,,"SEPARATE from F986-ND fuse. Matches PCB F1 footprint. Carried-forward exact selection; assembler must confirm land pattern, availability and orientation. No unapproved substitutions."
6,1,J1,Adafruit,1979,1528-1783-ND,Raspberry Pi extra-tall 40-pin stacking socket,Seizo_Reviewed:Pi_HAT_Stacking_Socket_Checked,THT,Bottom,,"Do not use 1979 as DigiKey SKU; check underside geometry Carried-forward exact selection; assembler must confirm land pattern, availability and orientation. No unapproved substitutions."
7,1,J8,GCT,USB4105-GF-A,2073-USB4105-GF-ACT-ND,USB-C 16-pin right-angle connector,Seizo_Reviewed:RC2_J8_USB4105_GND_Heel_Clearance,Hybrid (SMT contacts + THT shell),Top,,"Custom land pattern mechanical check required SMT signal pads and plated through-hole shield tabs; solder both. Do not treat mounting holes as SMT contacts. Carried-forward exact selection; assembler must confirm land pattern, availability and orientation. No unapproved substitutions."
8,1,C4,Samsung,CL31A226KPHNNNE,1276-1287-1-ND,22uF 10V X5R 1206,Seizo_Reviewed:RC2_C4_C_1206_3216Metric,SMT,Top,,"Verify cut-tape suffix against DigiKey page before purchase Carried-forward exact selection; assembler must confirm land pattern, availability and orientation. No unapproved substitutions."
9,1,C5,Samsung,CL21B104KBCNNNC,1276-1003-1-ND,100nF 50V X7R 0805,Seizo_Reviewed:RC2_C5_C_0805_2012Metric,SMT,Top,,"Verify cut-tape suffix against DigiKey page before purchase Carried-forward exact selection; assembler must confirm land pattern, availability and orientation. No unapproved substitutions."
10,1,R3,Yageo,RC0805FR-0710KL,311-10.0KCRCT-ND,10k 1% 0805 resistors,Seizo_Reviewed:RC2_R3_R_0805_2012Metric,SMT,Top,,"Replace reel SKU; verify exact CT SKU Carried-forward exact selection; assembler must confirm land pattern, availability and orientation. No unapproved substitutions."
11,1,R4,Yageo,RC0805FR-0710KL,311-10.0KCRCT-ND,10k 1% 0805 resistors,Seizo_Reviewed:RC2_R4_R_0805_2012Metric,SMT,Top,,"Replace reel SKU; verify exact CT SKU Carried-forward exact selection; assembler must confirm land pattern, availability and orientation. No unapproved substitutions."
12,1,R12,Yageo,RC0805FR-0710KL,311-10.0KCRCT-ND,10k 1% 0805 resistors,Seizo_Reviewed:RC2_R12_R_0805_2012Metric,SMT,Top,,"Replace reel SKU; verify exact CT SKU Carried-forward exact selection; assembler must confirm land pattern, availability and orientation. No unapproved substitutions."
13,1,R13,Yageo,RC0805FR-0710KL,311-10.0KCRCT-ND,10k 1% 0805 resistors,Seizo_Reviewed:RC2_R13_R_0805_2012Metric,SMT,Top,,"Replace reel SKU; verify exact CT SKU Carried-forward exact selection; assembler must confirm land pattern, availability and orientation. No unapproved substitutions."
14,1,R14,Yageo,RC0805FR-074K7L,311-4.70KCRCT-ND,4.7k 1% 0805 resistors,Seizo_Reviewed:RC2_R14_R_0805_2012Metric,SMT,Top,,"Replace reel SKU; verify exact CT SKU Carried-forward exact selection; assembler must confirm land pattern, availability and orientation. No unapproved substitutions."
15,1,R15,Yageo,RC0805FR-074K7L,311-4.70KCRCT-ND,4.7k 1% 0805 resistors,Seizo_Reviewed:RC2_R15_R_0805_2012Metric,SMT,Top,,"Replace reel SKU; verify exact CT SKU Carried-forward exact selection; assembler must confirm land pattern, availability and orientation. No unapproved substitutions."
16,1,R5,Bourns,CR0805-FX-5101ELF,CR0805-FX-5101ELFCT-ND,5.1k 1% 0805 resistors,Seizo_Reviewed:RC2_R5_R_0805_2012Metric,SMT,Top,,"USB-C CC pulldowns Carried-forward exact selection; assembler must confirm land pattern, availability and orientation. No unapproved substitutions."
17,1,R6,Bourns,CR0805-FX-5101ELF,CR0805-FX-5101ELFCT-ND,5.1k 1% 0805 resistors,Seizo_Reviewed:RC2_R6_R_0805_2012Metric,SMT,Top,,"USB-C CC pulldowns Carried-forward exact selection; assembler must confirm land pattern, availability and orientation. No unapproved substitutions."
18,1,R7,Yageo,RC0805FR-0722RL,311-22.0CRCT-ND,22 ohm 1% 0805 resistors,Seizo_Reviewed:RC2_R7_R_0805_2012Metric,SMT,Top,,"Verify exact cut-tape DigiKey code Carried-forward exact selection; assembler must confirm land pattern, availability and orientation. No unapproved substitutions."
19,1,R8,Yageo,RC0805FR-0722RL,311-22.0CRCT-ND,22 ohm 1% 0805 resistors,Seizo_Reviewed:RC2_R8_R_0805_2012Metric,SMT,Top,,"Verify exact cut-tape DigiKey code Carried-forward exact selection; assembler must confirm land pattern, availability and orientation. No unapproved substitutions."
20,1,R9,Yageo,RC0805FR-071KL,311-1.00KCRCT-ND,1k 1% 0805 resistor,Seizo_Reviewed:RC2_R9_R_0805_2012Metric,SMT,Top,,"Verify exact cut-tape DigiKey code Carried-forward exact selection; assembler must confirm land pattern, availability and orientation. No unapproved substitutions."
21,1,D1,Lite-On,LTST-C170KGKT,160-1414-1-ND,Green 0805 LED,Seizo_Reviewed:RC2_D1_LED_0805_2012Metric,SMT,Top,,"Verify CT suffix, polarity Carried-forward exact selection; assembler must confirm land pattern, availability and orientation. No unapproved substitutions."
22,1,SW1,E-Switch,TL3305AF160QG,EG5350CT-ND,SMD tactile switch TL3305A,Seizo_Reviewed:RC2_SW1_SW_SPST_TL3305A,SMT,Top,,"Verify exact cut-tape SKU and footprint Carried-forward exact selection; assembler must confirm land pattern, availability and orientation. No unapproved substitutions."
23,1,RESET1,E-Switch,TL3305AF160QG,EG5350CT-ND,SMD tactile switch TL3305A,Seizo_Reviewed:RC2_RESET1_SW_SPST_TL3305A,SMT,Top,,"Verify exact cut-tape SKU and footprint Carried-forward exact selection; assembler must confirm land pattern, availability and orientation. No unapproved substitutions."
24,1,U2,Espressif,ESP32-S3-WROOM-1-N8R8,5407-ESP32-S3-WROOM-1-N8R8CT-ND,ESP32-S3-WROOM-1-N8R8 8MB PSRAM module,Seizo_Reviewed:RC2_U2_ESP32_S3_WROOM_1_Thermal030,SMT,Top,https://www.digikey.com/en/products/detail/espressif-systems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,"Mouser part 356-EP32S3WROOM1N8R8. https://www.mouser.com/en/ProductDetail/Espressif-Systems/ES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 Exact ESP32-S3-WROOM-1-N8R8, 8MB flash and 8MB PSRAM, PCB antenna. Other parts remain on DigiKey purchasing list. Unit quote $6.28, shipping/tax/tariffs excluded. SMT module with exposed GND pad41 and open 0.30mm thermal vias; assembler must review stencil/paste-wicking process. Carried-forward exact selection; assembler must confirm land pattern, availability and orientation. No unapproved substitutions."
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
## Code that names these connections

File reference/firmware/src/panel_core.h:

// Reference firmware. No physical or actuator validation.
#pragma once
#include <stdint.h>
#include <stddef.h>

namespace seizo {
// Bits7/15 are logical transport slots, not MCP23017 input pins. The actual
// MCP23017 A7/B7 must remain outputs per current DS20001952D/erratum.
inline uint16_t composePanelInputs(uint16_t mcp14,bool lcd_vio,bool bb_fault_high){
  return (uint16_t)((mcp14&0x7f7f)|(lcd_vio?0x0080:0)|(bb_fault_high?0x8000:0));
}
class PanelIo {
 public:
  virtual ~PanelIo() {}
  virtual bool begin() = 0;
  virtual bool readInputs(uint16_t& value) = 0;
  virtual bool readAdc(uint8_t channel, uint16_t& value) = 0;
};
typedef void (*LineWriter)(const char*, void*);
enum class MeterState : uint8_t { Disabled, Unconfigured, Settling, Valid, IoFault, ReferenceFault, OutOfRange };
struct Snapshot {
  uint32_t ms=0, session=0, sequence=0;
  uint16_t inputs=0xffff, raw=0xffff, pressed=0;
  bool io_ok=false, host_ok=false, lcd_ok=false, breadboard_ok=false;
  bool hold=false, stop1=false, stop2=false, needs_ack=true;
  bool meter_configured=false;
  MeterState meter=MeterState::Disabled;
  uint16_t adc0=0, reference=0;
  int32_t millivolts=0, gain_ppm=1000000, zero_mv=0;
};
class PanelCore {
 public:
  static constexpr size_t MaxHostLine=79;
  static constexpr uint32_t HostTimeoutMs=1500, DebounceMs=20, MeterSettleMs=50;
  PanelCore(PanelIo& io, LineWriter writer, void* context=nullptr);
  bool begin(uint32_t now);
  void tick(uint32_t now);
  void handleHostLine(const char* line, uint32_t now);
  void onHostLine(const char* line, uint32_t now) { handleHostLine(line,now); }
  Snapshot snapshot() const { return state_; }
  // Only a deliberate local operator action may call this; never on reconnect.
  bool acknowledge(uint32_t now);
  void sendStatus();
 private:
  PanelIo& io_; LineWriter writer_; void* context_;
  Snapshot state_;
  uint16_t candidate_=0xffff, blocked_=0xffff;
  uint32_t changed_[16]={}, last_ping_=0, last_poll_=0, last_state_=0, meter_since_=0, last_meter_=0;
  bool seeded_=false, meter_enabled_=false, begun_=false, configured_=false;
  void output(const char* line);
  void inhibit();
  void updateInputs(uint16_t raw, uint32_t now);
  void updateMeter(uint32_t now);
  void emitEvent(const char* kind, int index, bool down);
  void error(const char* code);
};
const char* meterStateName(MeterState s);
}

#ifdef ARDUINO
#include <Arduino.h>
#include <Wire.h>
#include <SPI.h>
namespace seizo {
typedef bool (*SpiLock)(void*);
typedef void (*SpiUnlock)(void*);
class ArduinoPanelIo : public PanelIo {
 public:
  // Caller begins Wire/SPI and shares the same lock with display/touch adapters.
  ArduinoPanelIo(TwoWire& wire, SPIClass& spi, int adc_cs, const int* all_cs,
                 size_t count, int lcd_vio_pin, int bb_fault_pin,
                 SpiLock lock=nullptr, SpiUnlock unlock=nullptr, void* context=nullptr);
  bool begin() override;
  bool readInputs(uint16_t& value) override;
  bool readAdc(uint8_t channel, uint16_t& value) override;
 private:
  TwoWire& wire_; SPIClass& spi_; int adc_cs_; const int* all_cs_; size_t count_;
  int lcd_vio_pin_,bb_fault_pin_;
  SpiLock lock_; SpiUnlock unlock_; void* context_;
  bool writeReg(uint8_t address, uint8_t value);
  bool readReg(uint8_t address, uint8_t& value);
};
}
#endif
